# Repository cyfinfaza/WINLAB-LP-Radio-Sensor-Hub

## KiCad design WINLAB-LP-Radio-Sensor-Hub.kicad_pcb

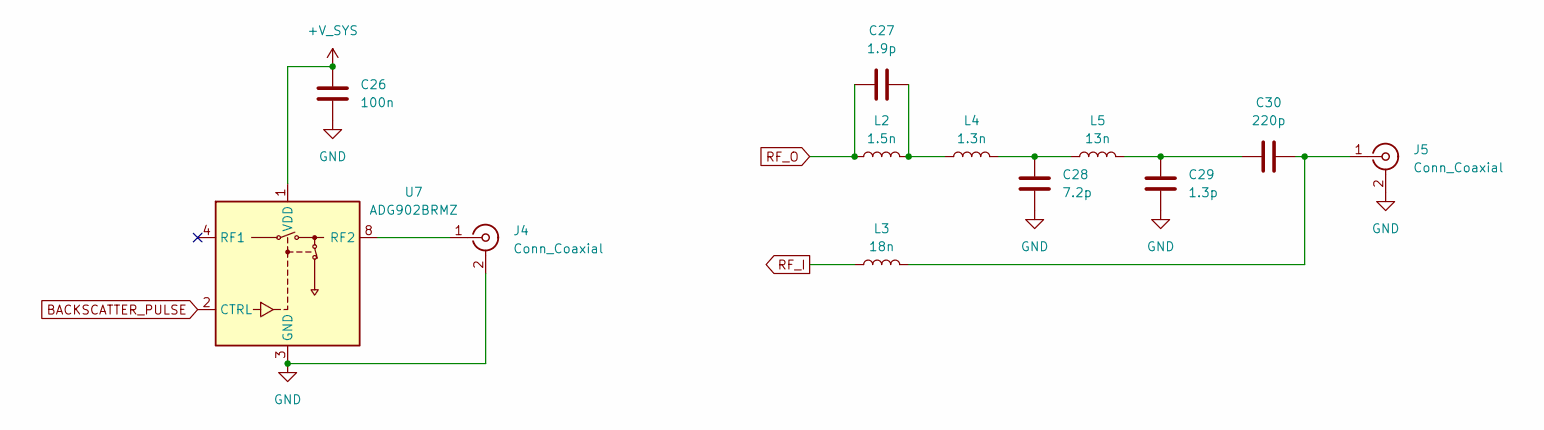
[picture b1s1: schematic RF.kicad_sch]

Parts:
C26: 100n; C_0603_1608Metric_Pad1.08x0.95mm_HandSolder
C27: 1.9p; C_0402_1005Metric
C28: 7.2p; C_0402_1005Metric
C29: 1.3p; C_0402_1005Metric
C30: 220p; C_0402_1005Metric
J4, J5: Conn_Coaxial; SMA_Molex_73251-2200_Horizontal
L2: 1.5n; L_0402_1005Metric
L3: 18n; L_0402_1005Metric
L4: 1.3n; L_0402_1005Metric
L5: 13n; L_0402_1005Metric
U7: ADG902BRMZ; MSOP-8_3x3mm_P0.65mm

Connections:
+V_SYS: C26.1, U7.1 (VDD); also elsewhere on the board
BACKSCATTER_PULSE: U7.2 (CTRL); also elsewhere on the board
GND: C26.2, C28.2, C29.2, J4.2 (Ext), J5.2 (Ext), U7.3 (GND), U7.5 (GND), U7.6 (GND), U7.7 (GND); also elsewhere on the board
unnamed: C27.2, L2.2, L4.1
unnamed: C28.1, L4.2, L5.1
unnamed: C29.1, C30.1, L5.2
unnamed: J4.1 (In), U7.8 (RF2)
unnamed: C30.2, J5.1 (In), L3.2
RF_I: L3.1; also elsewhere on the board
RF_O: C27.1, L2.1; also elsewhere on the board

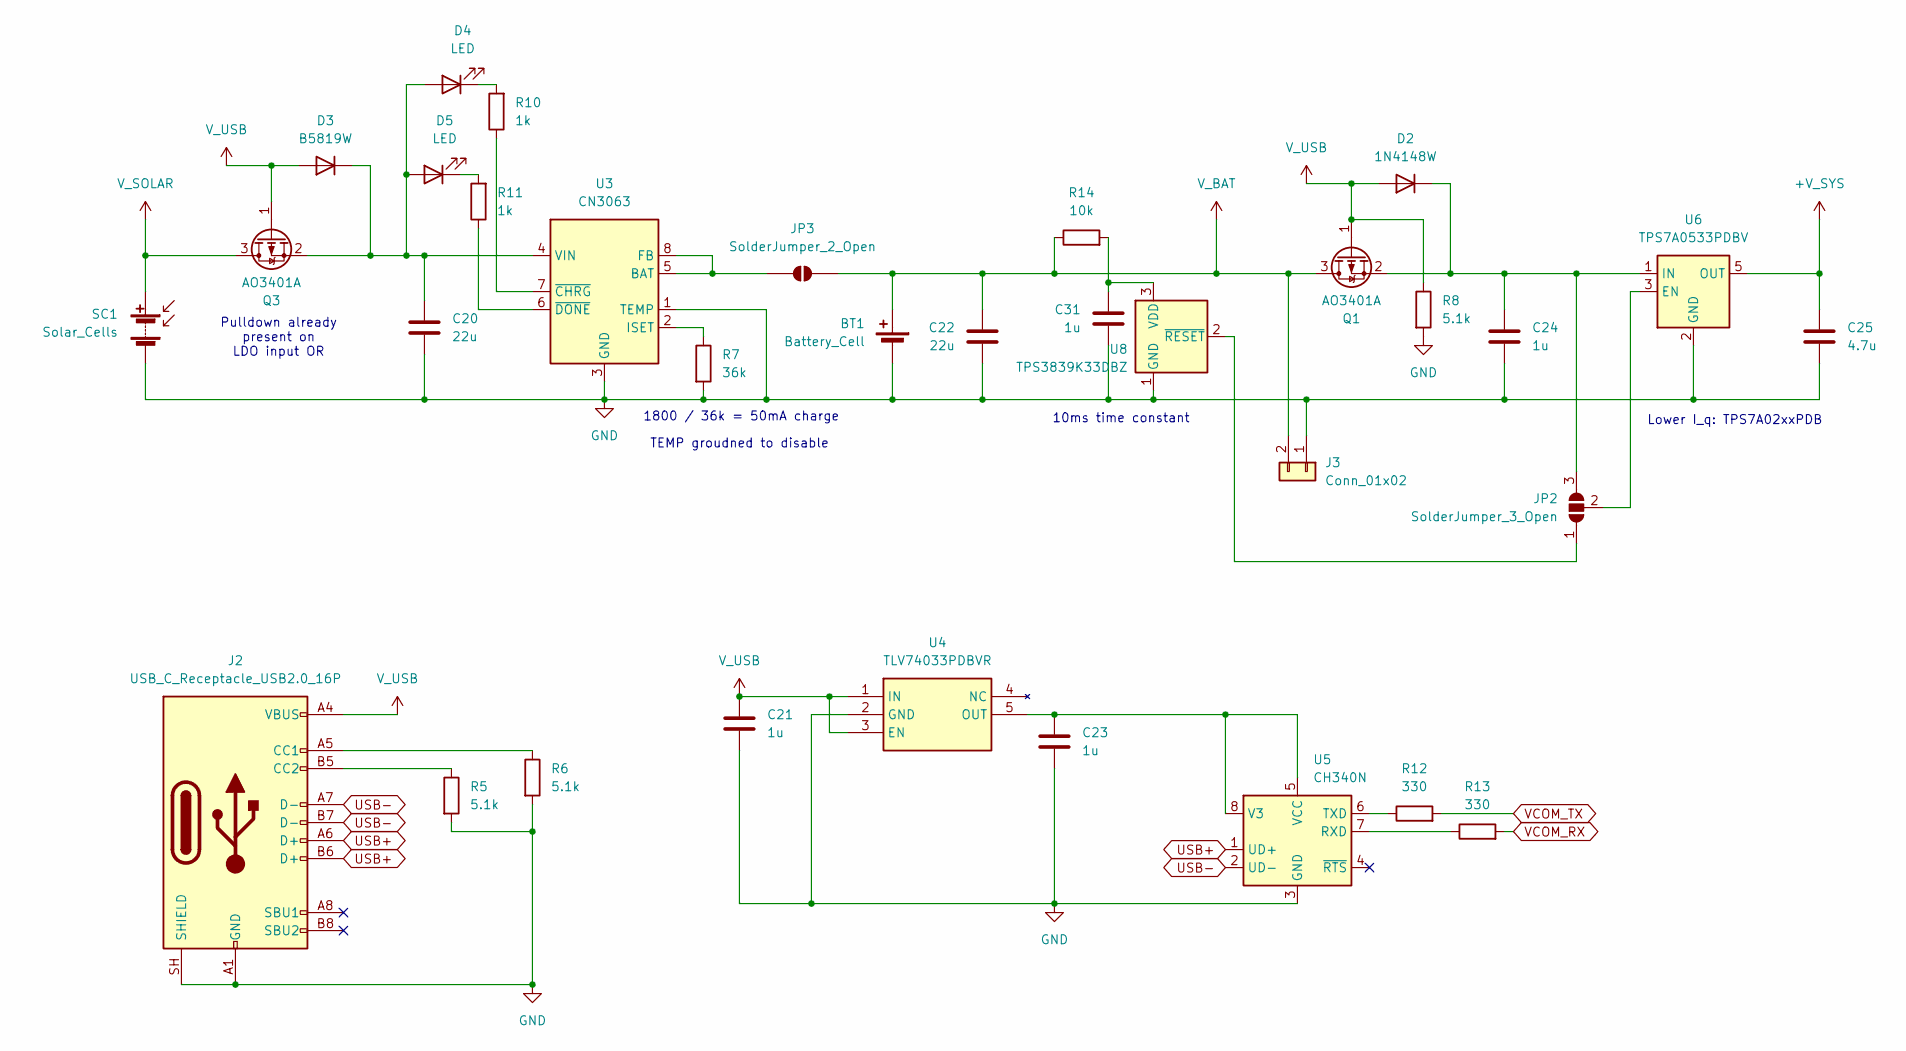
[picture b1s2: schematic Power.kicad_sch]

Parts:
BT1: Battery_Cell; BatteryHolder_Keystone_3008_1x2450
C20, C22: 22u; C_0805_2012Metric_Pad1.18x1.45mm_HandSolder
C21, C23, C24, C31: 1u; C_0603_1608Metric_Pad1.08x0.95mm_HandSolder
C25: 4.7u; C_0805_2012Metric_Pad1.18x1.45mm_HandSolder
D2: 1N4148W; D_SOD-123
D3: B5819W; D_SOD-123
D4, D5: LED; LED_0603_1608Metric_Pad1.05x0.95mm_HandSolder
J2: USB_C_Receptacle_USB2.0_16P; USB_C_Receptacle_GCT_USB4105-xx-A_16P_TopMnt_Horizontal
J3: Conn_01x02; PinHeader_1x02_P2.54mm_Vertical
JP2: SolderJumper_3_Open; SolderJumper-3_P1.3mm_Open_RoundedPad1.0x1.5mm
JP3: SolderJumper_2_Open; SolderJumper-2_P1.3mm_Open_RoundedPad1.0x1.5mm
Q1, Q3: AO3401A; SOT-23
R5, R6, R8: 5.1k; R_0603_1608Metric_Pad0.98x0.95mm_HandSolder
R7: 36k; R_0603_1608Metric_Pad0.98x0.95mm_HandSolder
R10, R11: 1k; R_0603_1608Metric_Pad0.98x0.95mm_HandSolder
R12, R13: 330; R_0603_1608Metric_Pad0.98x0.95mm_HandSolder
R14: 10k; R_0603_1608Metric_Pad0.98x0.95mm_HandSolder
SC1: Solar_Cells; JST_XH_B2B-XH-AM_1x02_P2.50mm_Vertical
U3: CN3063; SOIC-8-1EP_3.9x4.9mm_P1.27mm_EP2.41x3.3mm_ThermalVias
U4: TLV74033PDBVR; SOT95P280X145-5N; Mouser Part Number 595-TLV74033PDBVR
U5: CH340N; JEITA_SOIC-8_3.9x4.9mm_P1.27mm
U6: TPS7A0533PDBV; SOT-23-5
U8: TPS3839K33DBZ; SOT-23

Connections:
+V_SYS: C25.1, U6.5 (OUT); also elsewhere on the board
GND: BT1.2 (-), C20.2, C21.2, C22.2, C23.2, C24.2, C25.2, C31.2, J2.A1 (GND), J2.A12 (GND), J2.B1 (GND), J2.B12 (GND), J2.SH (SHIELD), J3.1, R5.2, R6.2, R7.2, R8.2, SC1.2 (-), U3.1 (TEMP), U3.3 (GND), U3.9 (GND), U4.2 (GND), U5.3 (GND), U6.2 (GND), U8.1 (GND); also elsewhere on the board
unnamed: C24.1, D2.1 (K), JP2.3 (B), Q1.2 (S), U6.1 (IN)
unnamed: C20.1, D3.1 (K), D4.2 (A), D5.2 (A), Q3.2 (S), U3.4 (VIN)
unnamed: D4.1 (K), R10.2
unnamed: D5.1 (K), R11.2
unnamed: J2.A5 (CC1), R6.1
unnamed: J2.B5 (CC2), R5.1
unnamed: JP2.1 (A), U8.2 (~RESET)
unnamed: JP2.2 (C), U6.3 (EN)
unnamed: JP3.1 (A), U3.5 (BAT), U3.8 (FB)
unnamed: R7.1, U3.2 (ISET)
unnamed: R10.1, U3.7 (~CHRG)
unnamed: R11.1, U3.6 (~DONE)
unnamed: C23.1, U4.5 (OUT), U5.5 (VCC), U5.8 (V3)
unnamed: R13.1, U5.7 (RXD)
unnamed: R12.1, U5.6 (TXD)
unnamed: C31.1, R14.2, U8.3 (VDD)
USB+: J2.A6 (D+), J2.B6 (D+), U5.1 (UD+)
USB-: J2.A7 (D-), J2.B7 (D-), U5.2 (UD-)
VCOM_RX: R13.2; also elsewhere on the board
VCOM_TX: R12.2; also elsewhere on the board
V_BAT: BT1.1 (+), C22.1, J3.2, JP3.2 (B), Q1.3 (D), R14.1
V_SOLAR: Q3.3 (D), SC1.1 (+)
V_USB: C21.1, D2.2 (A), D3.2 (A), J2.A4 (VBUS), J2.A9 (VBUS), J2.B4 (VBUS), J2.B9 (VBUS), Q1.1 (G), Q3.1 (G), R8.1, U4.1 (IN), U4.3 (EN)

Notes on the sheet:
Pulldown already present on LDO input OR
1800 / 36k = 50mA charge
Lower I_q: TPS7A02xxPDB
10ms time constant
TEMP groudned to disable

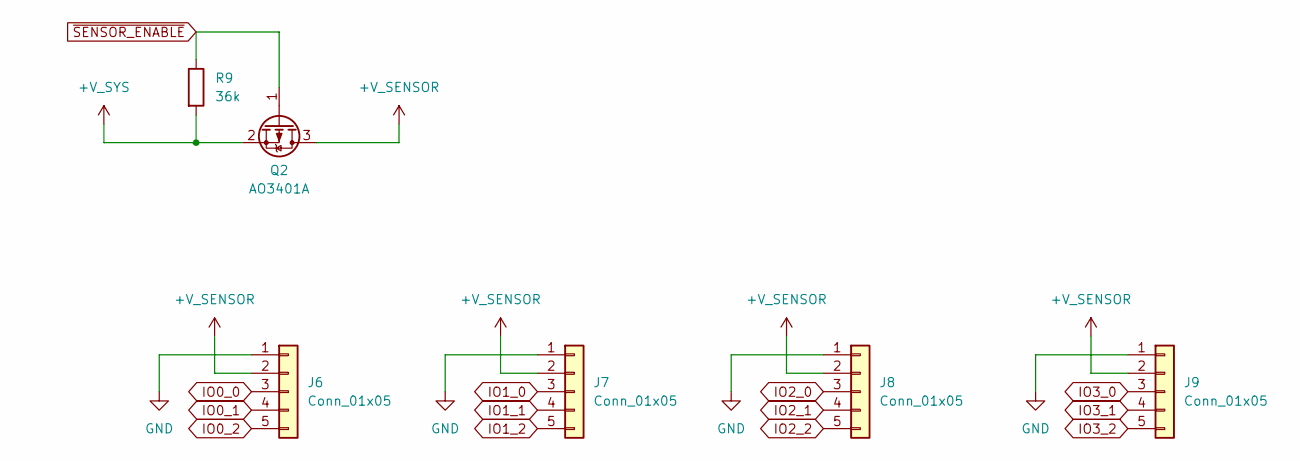
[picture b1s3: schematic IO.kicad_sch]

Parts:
J6, J7, J8, J9: Conn_01x05; JST_XH_B5B-XH-AM_1x05_P2.50mm_Vertical
Q2: AO3401A; SOT-23
R9: 36k; R_0603_1608Metric_Pad0.98x0.95mm_HandSolder

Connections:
+V_SENSOR: J6.2, J7.2, J8.2, J9.2, Q2.3 (D)
+V_SYS: Q2.2 (S), R9.2; also elsewhere on the board
GND: J6.1, J7.1, J8.1, J9.1; also elsewhere on the board
IO0_0: J6.3; also elsewhere on the board
IO0_1: J6.4; also elsewhere on the board
IO0_2: J6.5; also elsewhere on the board
IO1_0: J7.3; also elsewhere on the board
IO1_1: J7.4; also elsewhere on the board
IO1_2: J7.5; also elsewhere on the board
IO2_0: J8.3; also elsewhere on the board
IO2_1: J8.4; also elsewhere on the board
IO2_2: J8.5; also elsewhere on the board
IO3_0: J9.3; also elsewhere on the board
IO3_1: J9.4; also elsewhere on the board
IO3_2: J9.5; also elsewhere on the board
~SENSOR_ENABLE: Q2.1 (G), R9.1; also elsewhere on the board

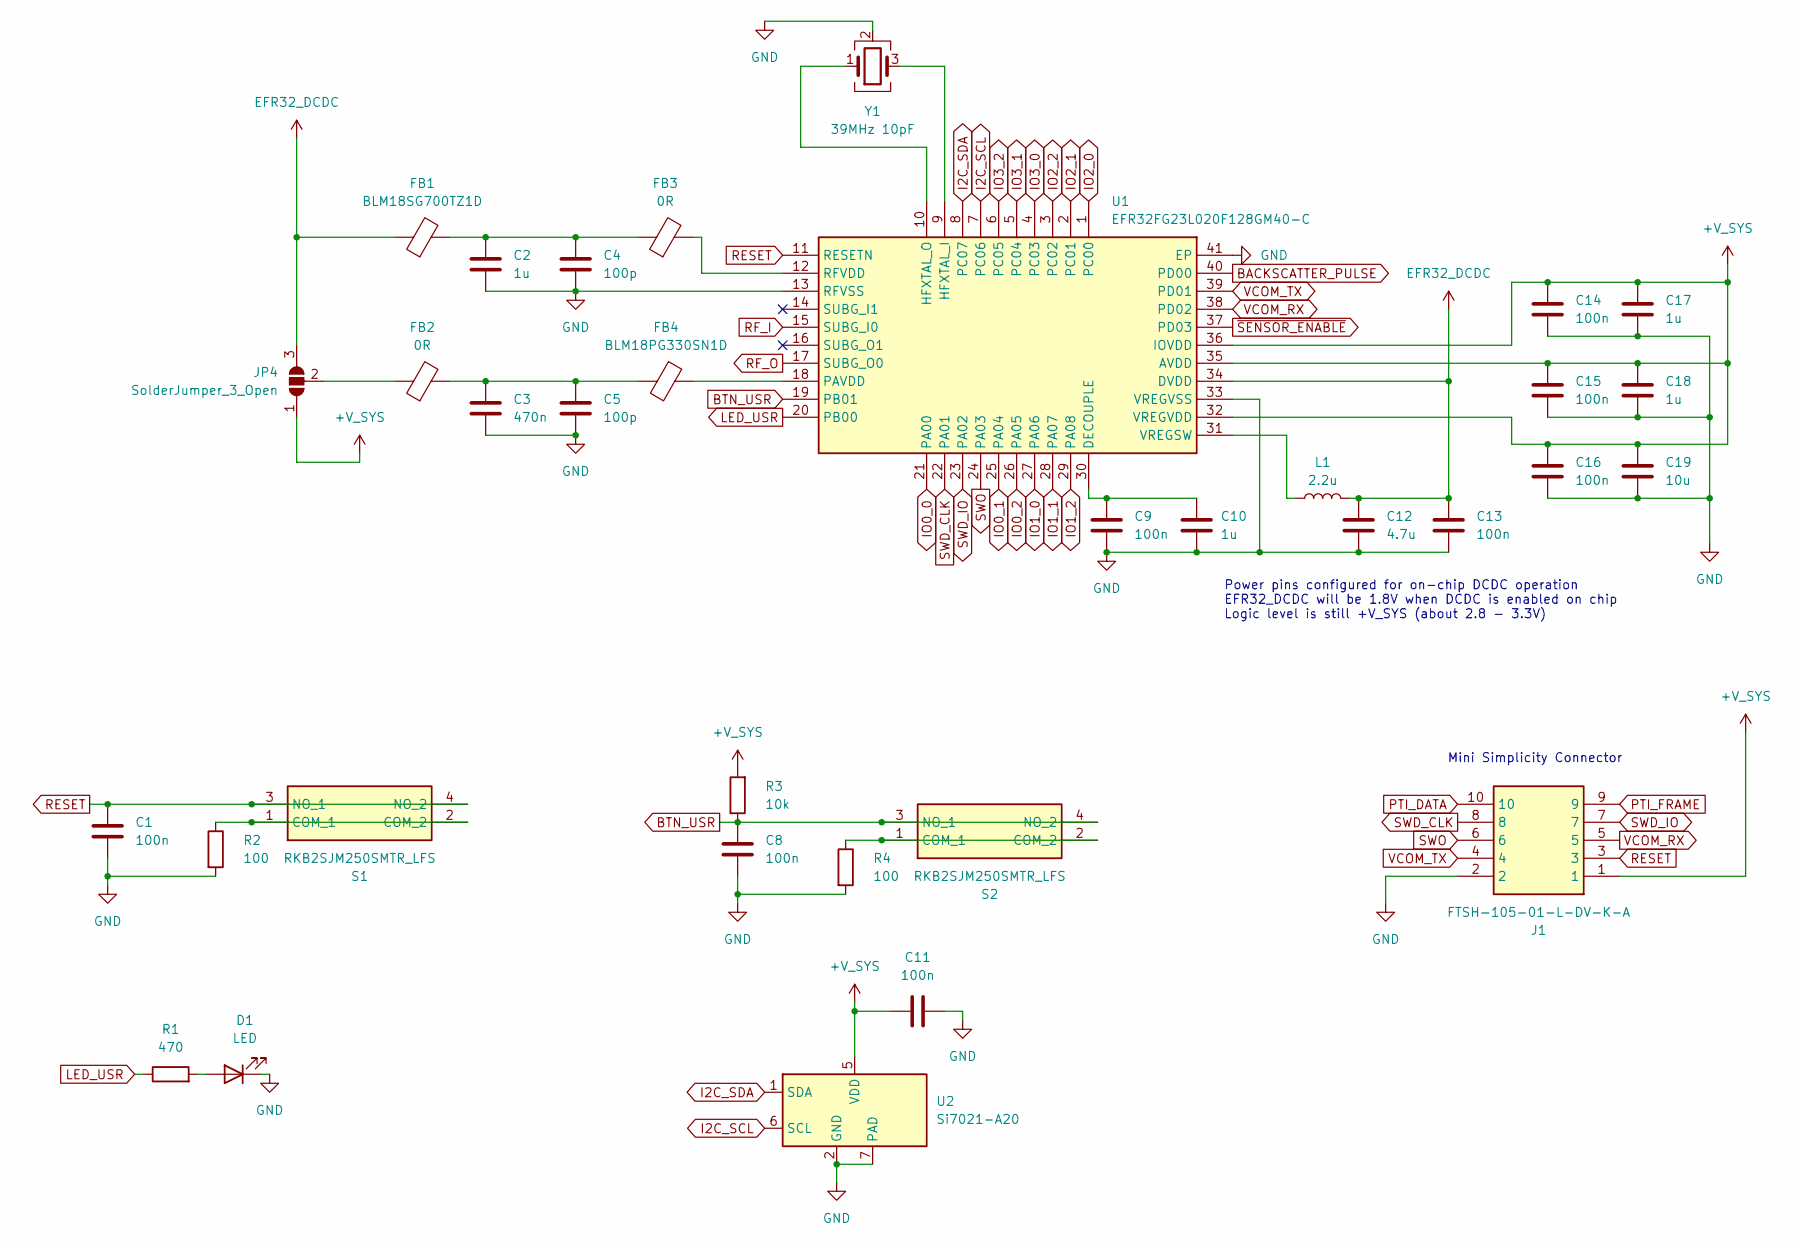
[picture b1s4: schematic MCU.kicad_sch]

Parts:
C1, C8, C9, C11, C13, C14, C15, C16: 100n; C_0603_1608Metric_Pad1.08x0.95mm_HandSolder
C2, C10, C17, C18: 1u; C_0603_1608Metric_Pad1.08x0.95mm_HandSolder
C3: 470n; C_0603_1608Metric_Pad1.08x0.95mm_HandSolder
C4, C5: 100p; C_0603_1608Metric_Pad1.08x0.95mm_HandSolder
C12: 4.7u; C_0805_2012Metric_Pad1.18x1.45mm_HandSolder
C19: 10u; C_0603_1608Metric_Pad1.08x0.95mm_HandSolder
D1: LED; LED_0603_1608Metric_Pad1.05x0.95mm_HandSolder
FB1: BLM18SG700TZ1D; L_0603_1608Metric_Pad1.05x0.95mm_HandSolder
FB2, FB3: 0R; L_0603_1608Metric_Pad1.05x0.95mm_HandSolder
FB4: BLM18PG330SN1D; L_0603_1608Metric_Pad1.05x0.95mm_HandSolder
J1: FTSH-105-01-L-DV-K-A; FTSH-105-XX-YYY-DV-K-A; Mouser Part Number 200-FTSH10501LDVKA
JP4: SolderJumper_3_Open; SolderJumper-3_P1.3mm_Open_RoundedPad1.0x1.5mm
L1: 2.2u; L_APV_ANR3015
R1: 470; R_0603_1608Metric_Pad0.98x0.95mm_HandSolder
R2, R4: 100; R_0603_1608Metric_Pad0.98x0.95mm_HandSolder
R3: 10k; R_0603_1608Metric_Pad0.98x0.95mm_HandSolder
S1, S2: RKB2SJM250SMTR_LFS; RKB2SJM250SMTRLFS; Mouser Part Number 611-RKB2SJM250SMTRLF
U1: EFR32FG23L020F128GM40-C; QFN-40-1EP_5x5mm_P0.4mm_EP3.6x3.6mm; Manufacturer_Part_Number EFR32FG23L020F128GM40-C
U2: Si7021-A20; DFN-6-1EP_3x3mm_P1mm_EP1.5x2.4mm
Y1: 39MHz 10pF; Crystal_SMD_2016-4Pin_2.0x1.6mm

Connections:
+V_SYS: C11.1, C14.1, C15.1, C16.1, C17.1, C18.1, C19.1, J1.1, JP4.1 (A), R3.2, U1.32 (VREGVDD), U1.35 (AVDD), U1.36 (IOVDD), U2.5 (VDD); also elsewhere on the board
BACKSCATTER_PULSE: U1.40 (PD00); also elsewhere on the board
BTN_USR: C8.1, R3.1, S2.3 (NO_1), S2.4 (NO_2), U1.19 (PB01)
EFR32_DCDC: C12.1, C13.1, FB1.1, JP4.3 (B), L1.2, U1.34 (DVDD)
GND: C1.2, C2.2, C3.2, C4.2, C5.2, C8.2, C9.2, C10.2, C11.2, C12.2, C13.2, C14.2, C15.2, C16.2, C17.2, C18.2, C19.2, D1.1 (K), J1.2, R2.2, R4.2, U1.13 (RFVSS), U1.33 (VREGVSS), U1.41 (EP), U2.2 (GND), U2.7 (PAD), Y1.2 (G), Y1.4 (G); also elsewhere on the board
I2C_SCL: U1.7 (PC06), U2.6 (SCL)
I2C_SDA: U1.8 (PC07), U2.1 (SDA)
IO0_0: U1.21 (PA00); also elsewhere on the board
IO0_1: U1.25 (PA04); also elsewhere on the board
IO0_2: U1.26 (PA05); also elsewhere on the board
IO1_0: U1.27 (PA06); also elsewhere on the board
IO1_1: U1.28 (PA07); also elsewhere on the board
IO1_2: U1.29 (PA08); also elsewhere on the board
IO2_0: U1.1 (PC00); also elsewhere on the board
IO2_1: U1.2 (PC01); also elsewhere on the board
IO2_2: U1.3 (PC02); also elsewhere on the board
IO3_0: U1.4 (PC03); also elsewhere on the board
IO3_1: U1.5 (PC04); also elsewhere on the board
IO3_2: U1.6 (PC05); also elsewhere on the board
LED_USR: R1.1, U1.20 (PB00)
unnamed: C2.1, C4.1, FB1.2, FB3.1
unnamed: C3.1, C5.1, FB2.2, FB4.2
unnamed: D1.2 (A), R1.2
unnamed: FB2.1, JP4.2 (C)
unnamed: R2.1, S1.1 (COM_1), S1.2 (COM_2)
unnamed: R4.1, S2.1 (COM_1), S2.2 (COM_2)
unnamed: C9.1, C10.1, U1.30 (DECOUPLE)
unnamed: U1.9 (HFXTAL_I), Y1.3
unnamed: U1.10 (HFXTAL_O), Y1.1
unnamed: FB4.1, U1.18 (PAVDD)
unnamed: FB3.2, U1.12 (RFVDD)
unnamed: L1.1, U1.31 (VREGSW)
PTI_DATA: J1.10
PTI_FRAME: J1.9
RESET: C1.1, J1.3, S1.3 (NO_1), S1.4 (NO_2), U1.11 (RESETN)
RF_I: U1.15 (SUBG_I0); also elsewhere on the board
RF_O: U1.17 (SUBG_O0); also elsewhere on the board
SWD_CLK: J1.8, U1.22 (PA01)
SWD_IO: J1.7, U1.23 (PA02)
SWO: J1.6, U1.24 (PA03)
VCOM_RX: J1.5, U1.38 (PD02); also elsewhere on the board
VCOM_TX: J1.4, U1.39 (PD01); also elsewhere on the board
~SENSOR_ENABLE: U1.37 (PD03); also elsewhere on the board

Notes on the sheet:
Power pins configured for on-chip DCDC operation EFR32_DCDC will be 1.8V when DCDC is enabled on chip Logic level is still +V_SYS (about 2.8 - 3.3V)
Mini Simplicity Connector

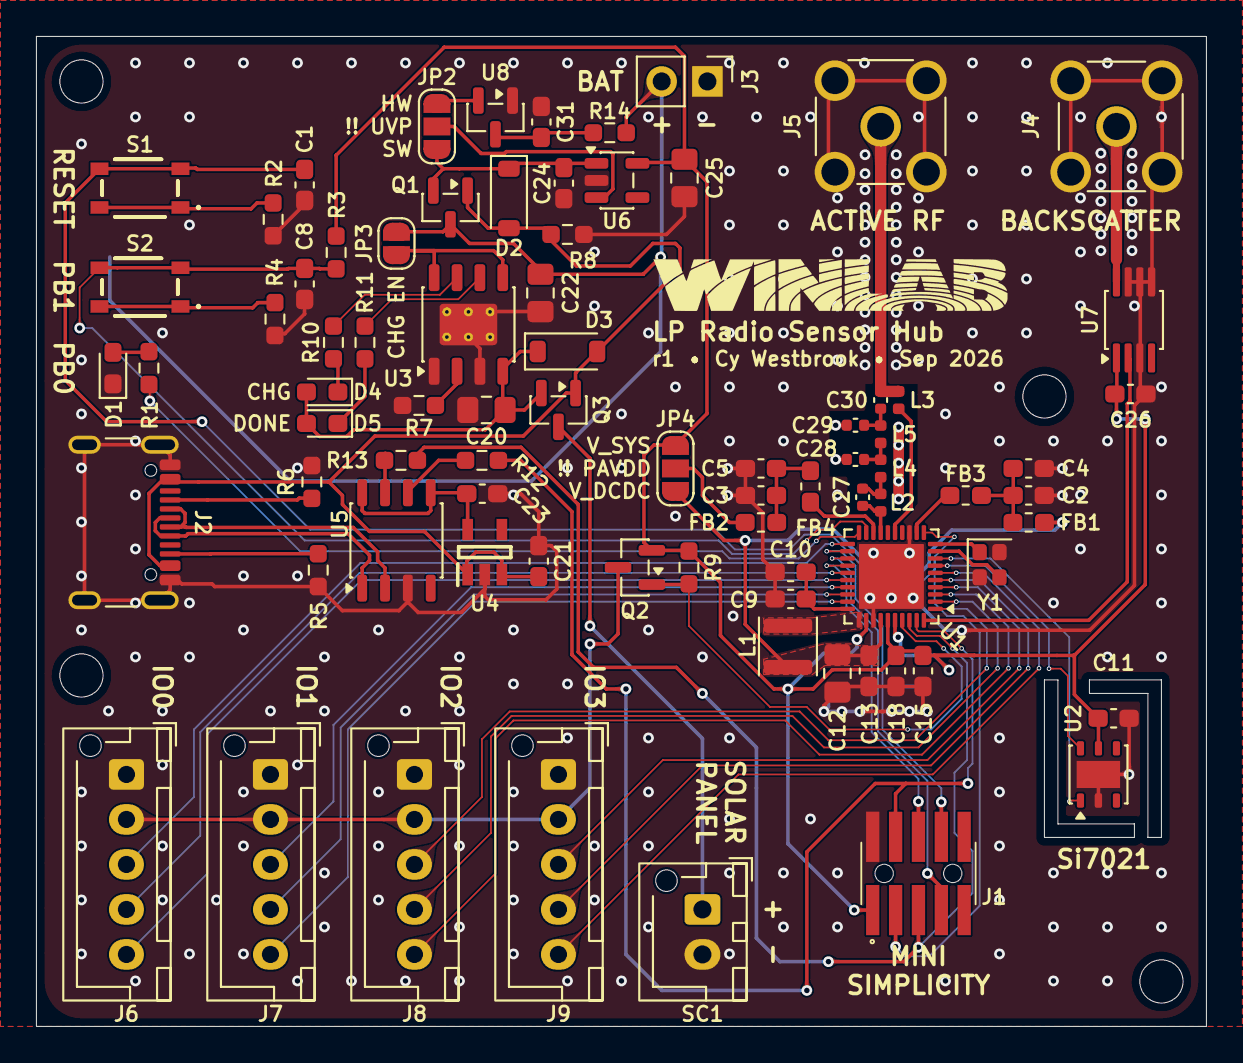
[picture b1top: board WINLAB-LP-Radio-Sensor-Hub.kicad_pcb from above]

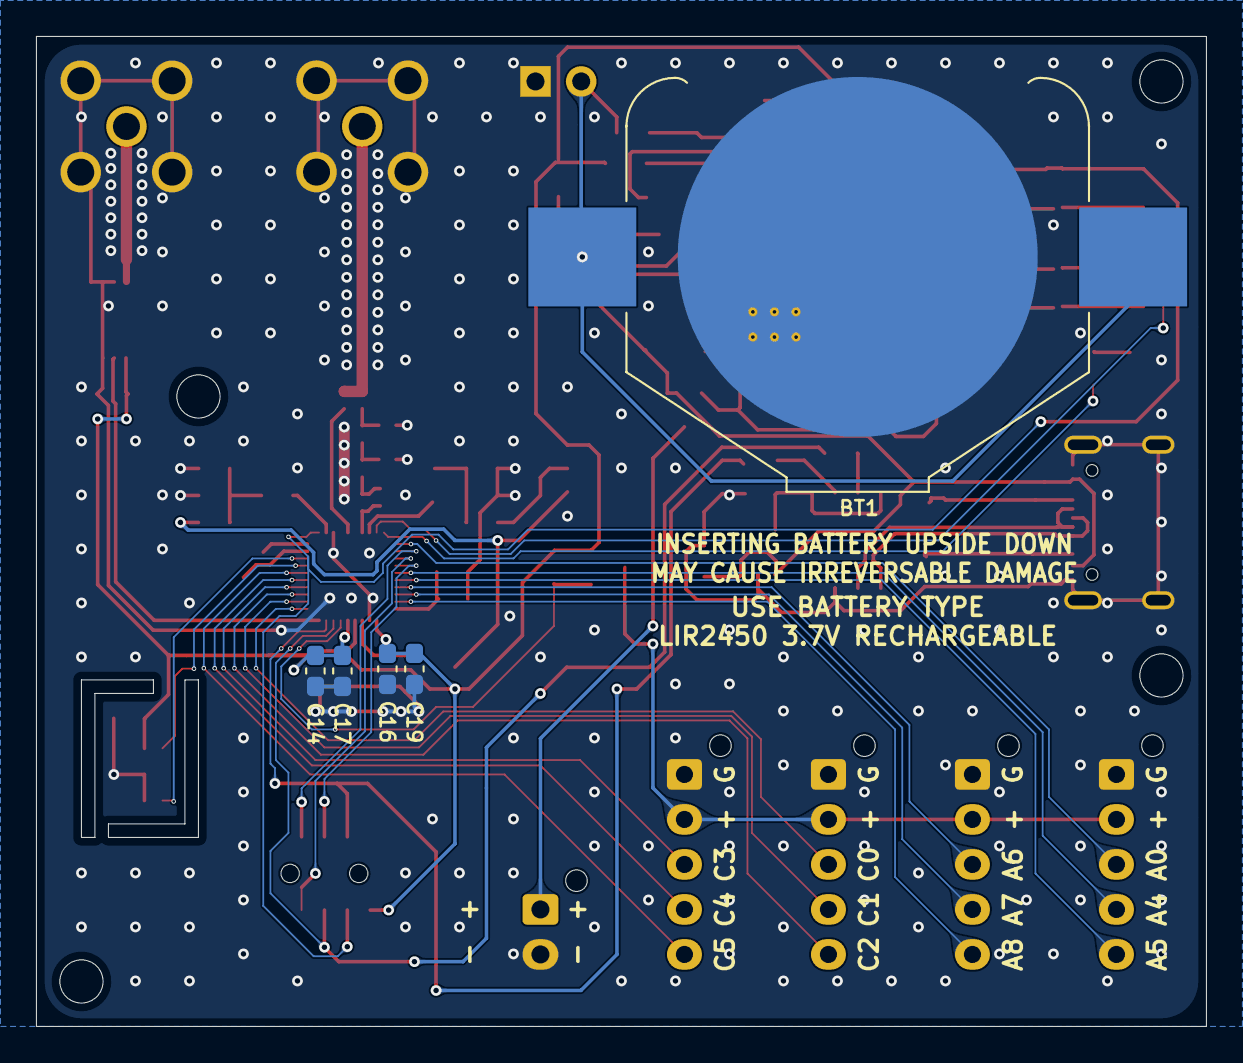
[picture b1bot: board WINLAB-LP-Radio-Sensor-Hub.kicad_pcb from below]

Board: 2 copper layers, 65.0 x 55.0 mm, 85 parts (5 on the bottom side), 68 nets.

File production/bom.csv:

Designator,Footprint,Quantity,Value,LCSC Part #
BT1,BatteryHolder_Keystone_3008_1x2450,1,Battery_Cell,
"C1, C11, C13, C14, C15, C16, C26, C8, C9",0603,9,100n,
"C10, C17, C18, C19, C2, C21, C23, C24, C25",0603,9,1u,
"C12, C22",0805,2,4.7u,
C20,0805,1,22u,
C27,0402,1,1.9p,
C28,0402,1,7.2p,
C29,0402,1,1.3p,
C3,0603,1,470n,
C30,0402,1,220p,
"C4, C5",0603,2,100p,
"C6, C7",0603,2,12p,
D1,0603,1,LED,
D2,D_SOD-123,1,1N4148W,
"FB1, FB2, FB3, FB4",0603,4,FerriteBead,
J1,FTSH-105-XX-YYY-DV-K-A,1,FTSH-105-01-L-DV-K-A,
J2,USB_C_Receptacle_GCT_USB4105-xx-A_16P_TopMnt_Horizontal,1,USB_C_Receptacle_USB2.0_16P,
J3,PinHeader_1x02_P2.54mm_Vertical,1,Conn_01x02,
"J4, J5",SMA_Molex_73251-2200_Horizontal,2,Conn_Coaxial,
"J6, J7, J8, J9",JST_XH_B5B-XH-AM_1x05_P2.50mm_Vertical,4,Conn_01x05,
L1,L_APV_ANR3015,1,2.2u,
L2,0402,1,1.5n,
L3,0402,1,18n,
L4,0402,1,1.3n,
L5,0402,1,13n,
"Q1, Q2",SOT-23,2,AO3401A,
R1,0603,1,470,
"R2, R4",0603,2,100,
R3,0603,1,10k,
"R5, R6",0603,2,5.1k,
"R7, R8, R9",0603,3,36k,
"S1, S2",RKB2SJM250SMTRLFS,2,RKB2SJM250SMTR_LFS,
SC1,JST_XH_B2B-XH-AM_1x02_P2.50mm_Vertical,1,Solar_Cells,
U1,QFN-40-1EP_5x5mm_P0.4mm_EP3.6x3.6mm,1,EFR32FG23L020F128GM40-C,
U2,DFN-6-1EP_3x3mm_P1mm_EP1.5x2.4mm,1,Si7021-A20,
U3,SOIC-8-1EP_3.9x4.9mm_P1.27mm_EP2.41x3.3mm_ThermalVias,1,CN3063,
U4,SOT95P280X145-5N,1,TLV74033PDBVR,
U5,JEITA_SOIC-8_3.9x4.9mm_P1.27mm,1,CH340N,
U6,SOT-23-5,1,TPS7A0522PDBV,
U7,MSOP-8_3x3mm_P0.65mm,1,ADG902BRMZ,
Y1,Crystal_SMD_2016-4Pin_2.0x1.6mm,1,39MHz 10pF,

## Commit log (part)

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2026-06-04 debug connector and buttons
2026-06-17 add backscatter and active radio components
2026-06-18 add initial pinouts and USB
2026-06-23 add IO ports, begin layout
2026-06-24 minor schematic changes
2026-06-29 initial layout and dense routing near chip
2026-06-30 more layout and routing work
2026-06-30 minor layout tweaks, add external power header
